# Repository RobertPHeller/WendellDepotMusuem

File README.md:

# Wendell Historical Society Musuem at Wendell Depot

This is a proposed model railroad layout at the Wendell Historical Society
Musuem at Wendell Depot. It models the section of the old B&M Railroad that
goes through Wendell Depot. It will be placed at the large display windows at
the from of the musuem. The view will be the view south from a point just
north of the tracks, centered on Wendell Depot Road. Features include crossing
gates across Wendell Depot Road and a railroad bridge over the Millers River
near the "west" end.  Also a portion of Wendell Depot Road, West Orange Road, 
and Kentfield Road and the various buildings that make up the village of 
Wendell Depot.

The layout is actually a oval that is 6 ft. by 14 ft., with 10 ft. "visible" 
and the rest of the layout "hidden".  At the back is a four track "staging" 
yard, where up to 4 trains (two eastbound and two westbound) can be made up. 
The layout will be set up with automated operation, with the 4 trains running 
one at a time through the "visible" section in alterniting directions.

- Satelite Map View: 

- OpenRailway Map: 

- Actual layout (XtrakCAD): 

## Files

- XtrakCAD file: WendellDepot.xtc 

- MRR System Layout Control DB file: WendellDepot.xml

- Benchwork (FreeCAD): Benchwork.py

- Software directory: [Software](Software/README.md) 

- JMRI PanelPro CTC Panel: [PanelPro](PanelPro/README.md)

- CATS CTC Panel: [CATS](CATS/README.md)

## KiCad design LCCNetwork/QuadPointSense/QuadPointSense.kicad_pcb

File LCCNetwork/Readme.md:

# LCC Network: layout automation

The LCC network will contain:

- 5 STM32F303-RIR4 boards with 5 STM32F303-Nucelo dev boards and 6 Aztrax RIR4 
shields. 
- 3 Quad Point Sense I/O modules
- 1 RR-CirKits Signal LCC-32H
- 2 RR-CirKits Signal LCC-s
- 1 LCC command station (TCS CS-105?)
- 1 Raspberry Pi 4 or 5 w/ monitor, keyboard, and mouse
- at least one throtle
- at least 10 Cat5/6 cables.

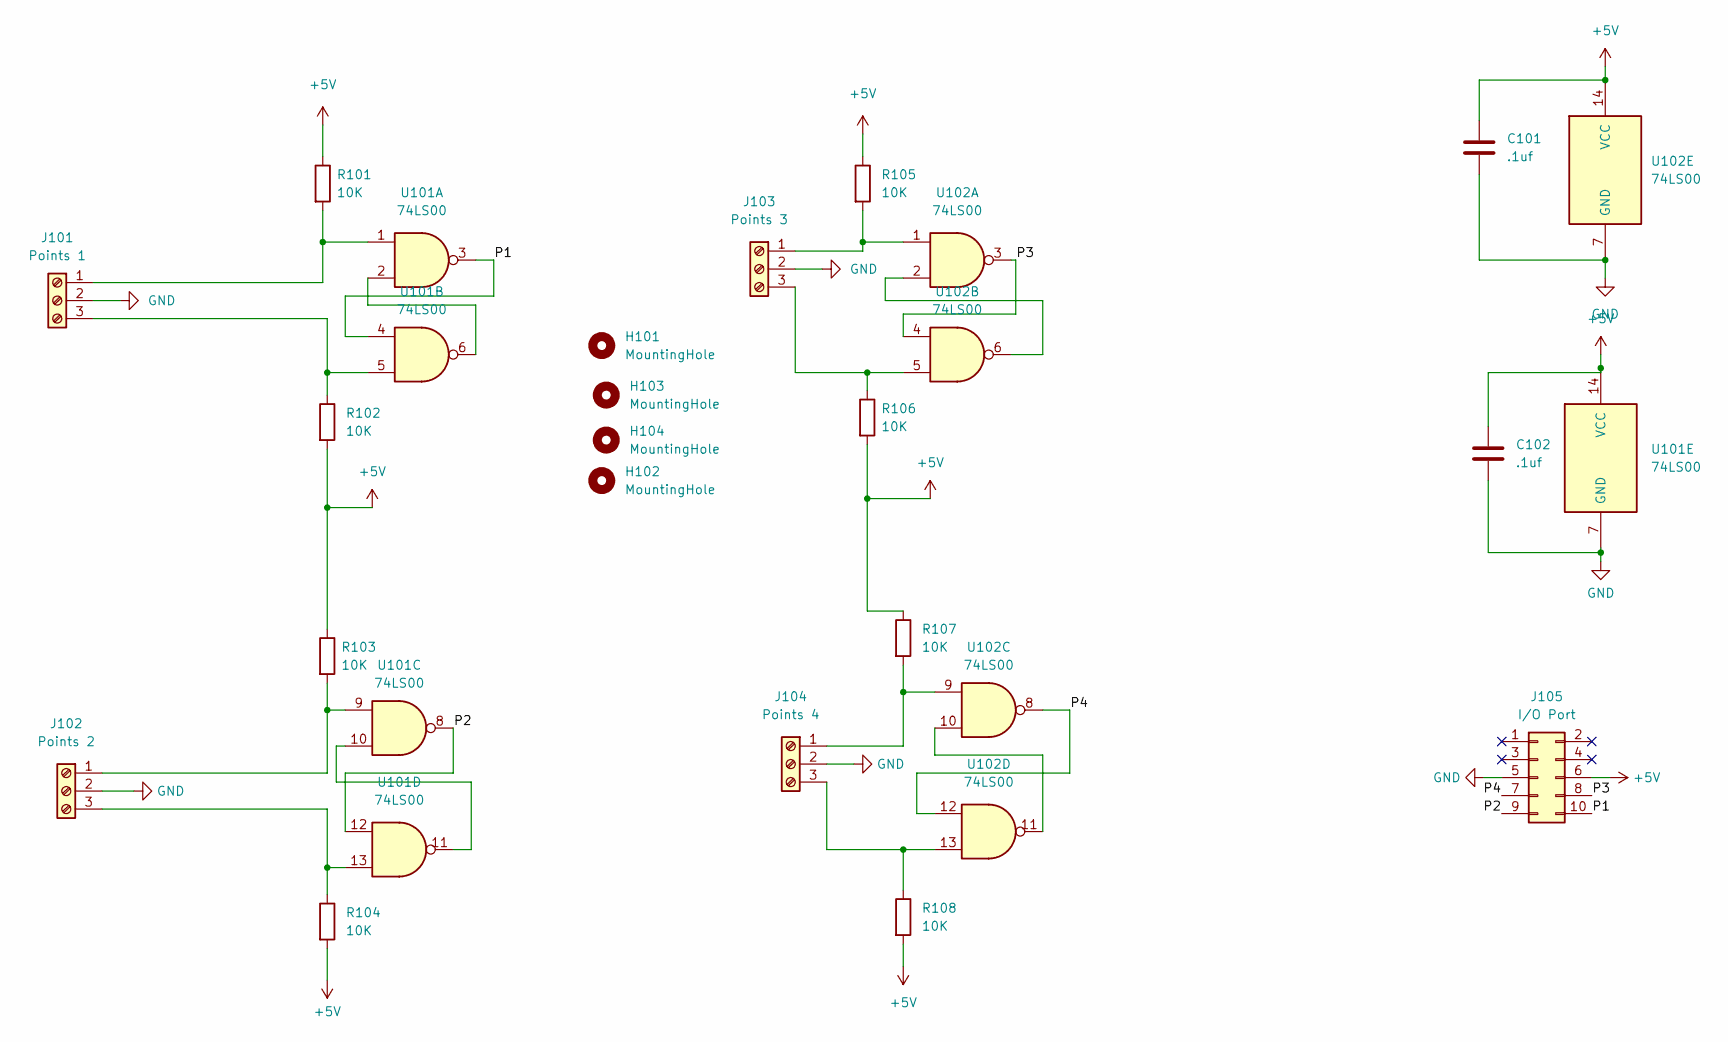
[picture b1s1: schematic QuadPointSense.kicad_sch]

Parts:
C101, C102: .1uf; C_0603_1608Metric; Mouser Part Number 581-KAM15AR71C104KM
H101, H102, H103, H104: MountingHole; MountingHole_3.5mm
J101: Points 1; TerminalBlock_TE_282834-3_1x03_P2.54mm_Horizontal
J102: Points 2; TerminalBlock_TE_282834-3_1x03_P2.54mm_Horizontal
J103: Points 3; TerminalBlock_TE_282834-3_1x03_P2.54mm_Horizontal
J104: Points 4; TerminalBlock_TE_282834-3_1x03_P2.54mm_Horizontal
J105: I/O Port; IDC-Header_2x05_P2.54mm_Vertical
R101, R102, R103, R104, R105, R106, R107, R108: 10K; R_0603_1608Metric; Mouser Part Number 603-AC0603DR-0710KL
U101, U102: 74LS00; SOIC-14_3.9x8.7mm_P1.27mm; Mouser Part Number 595-SN74LS00DR

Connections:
+5V: C101.1, C102.1, J105.6, R101.1, R102.2, R103.1, R104.2, R105.1, R106.2, R107.1, R108.2, U101.14 (VCC), U102.14 (VCC)
/P1: J105.10, U101.3, U101.4
/P2: J105.9, U101.8, U101.12
/P3: J105.8, U102.3, U102.4
/P4: J105.7, U102.8, U102.12
GND: C101.2, C102.2, J101.2, J102.2, J103.2, J104.2, J105.5, U101.7 (GND), U102.7 (GND)
unnamed: J101.1, R101.2, U101.1
unnamed: J101.3, R102.1, U101.5
unnamed: J102.1, R103.2, U101.9
unnamed: J102.3, R104.1, U101.13
unnamed: J103.1, R105.2, U102.1
unnamed: J103.3, R106.1, U102.5
unnamed: J104.1, R107.2, U102.9
unnamed: J104.3, R108.1, U102.13
unnamed: U101.2, U101.6
unnamed: U101.10, U101.11
unnamed: U102.2, U102.6
unnamed: U102.10, U102.11

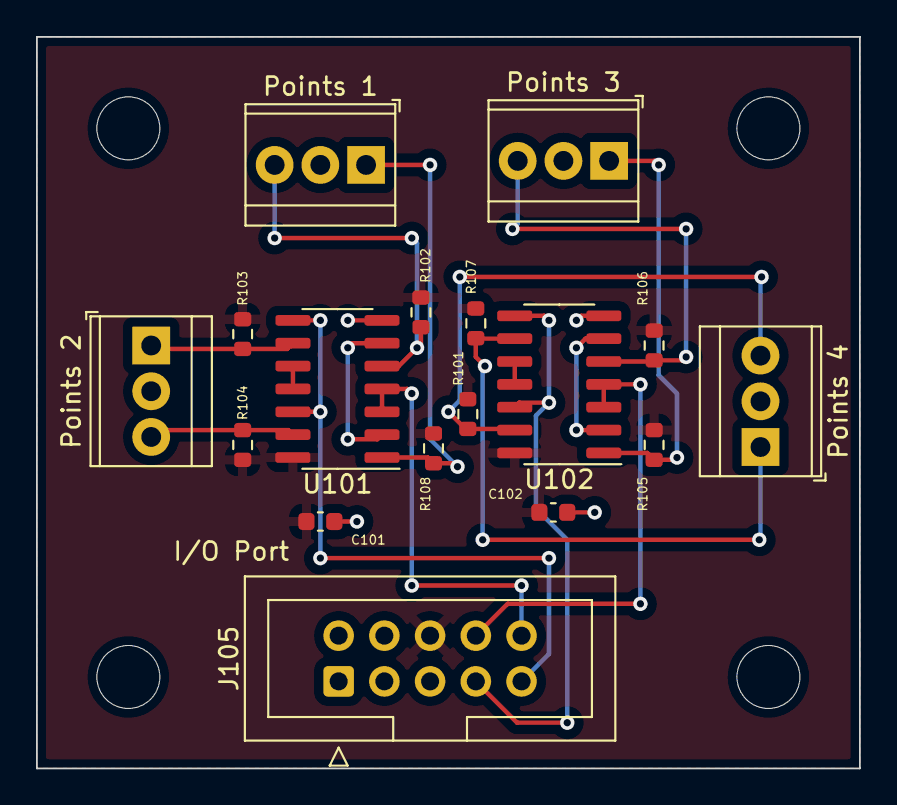
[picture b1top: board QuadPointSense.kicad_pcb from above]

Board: 2 copper layers, 45.7 x 40.6 mm, 21 parts (0 on the bottom side), 18 nets.

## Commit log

2023-04-09 Initial commit.
2023-04-09 Add Optical Sensors, create Layout Control DB.
2023-04-09 Add License and README.
2023-05-02 Start on 3D CAD model of the Benchwork.
2023-05-02 Add plywood and foam sheets.
2023-05-02 Add backdrops.
2024-12-09 Update as single track through Wendell Depot.
2024-12-09 Add additional sensors.
2024-12-10 Start on documentation.
2024-12-10 Start adding LCC Network nodes.
2024-12-10 Quad point sense input board.
2024-12-11 Add layout control elements.
2024-12-11 Basic framework for software.
2024-12-11 Add .gitignore.
2024-12-18 Adding Signals.
2025-01-05 Complete adding signals.
2025-01-05 Add Layout Control Configuration code.
2025-01-05 Add low-level producers and consumers.
2025-01-05 Add SimpleStackNoCDI code. Flesh out main.cxx.
2025-01-05 Start on RunATrainFlow.
2025-01-06 Complete OpticalLocationSensor and Signal, base functionallity of RunATrain.
2025-01-06 Add 0X prefix for hexx constants.
2025-01-06 Code in eventids.
2025-01-07 Add Check Sensors initial state.
2025-01-07 Add to do documentation.
2025-02-14 Add dispatcher panel for manual running.
2025-02-14 Start on Webserver.
2025-02-14 Initializer generator.
2025-02-14 Update Initialization code. Remove unneeded SimpleStackNoCDI code.
2025-02-16 Complete dispatcher panel for manual running.
2025-02-16 Working on DispatcherLogic for dispatcher panel for manual running.
2025-02-21 Complete CTC Panel for manual running.
2025-02-21 Route Code generator.
2025-02-21 Working on auto train running program.
2025-02-22 Complete RunATrainFlow, working on webserver.
2025-02-25 Working on route clearing code.
2025-02-25 Add -d (docroot) cli option.
2025-02-25 Complete route clearing, add featues to web interface.
2025-02-26 Completed RunATrainFlow.
2025-02-26 Update README.
2025-02-26 Fix event number issue (dup event numbers).
2025-02-27 Normalize LOG/debug statements.Q
2025-02-27 Add static webcontent.
2025-02-27 And cancel trains function.
2025-03-02 Update webserver appearence.
2025-03-17 Add httpd module.
2025-04-18 Add layers to map.
2025-04-19 Start JMRI/CATS setup. Create WendellDepot-JMRI.xml from WendellDepot.xml. Start WendellDepot-CATS.xml with Designer.
2025-04-19 Working on WendellDepot-CATS.xml with Designer.
2025-04-19 Completed tracks, blocks, and points on WendellDepot-CATS.xml with Designer.
2025-04-19 Add Signal Masts to JMRI table file.
2025-04-19 Connect ends, start on signals.
2025-04-19 Starting to add signals.
2025-04-20 Completed Panel.
2025-04-21 Update route selected commands.
2025-04-22 Clean up layout, re-position signals, and re-configure signal templates.
2025-04-22 Add labels.
2025-04-25 Add JMRI CTC Panel.
2025-04-26 Add Blocks and virtual occupancy detector sensors.
2025-04-26 Add Optical Block Occupancy (JMRI CTC version) jython script.
2025-04-26 Add comments to script.
2025-04-27 Move CATS and PanelPro to separate directories.
2025-04-27 Update READMEs.
2025-04-28 Alternitive Occupancy script, using signal masts instead of CTC Signal Lamps.
2025-05-16 Add Init.py for WendellDepot-JMRI-withPanel.xml.
2025-05-16 "Bind" Init.py to WendellDepot-JMRI-withPanel.xml using LogixNG.
